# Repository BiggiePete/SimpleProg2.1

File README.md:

# SimpleProg2.1
Simple Prog is a ST-LINK 2.1 esque programmer setup, using a simple PCB board, a 3d printed "clip" design, and a spring, the purpose of this is to intorduce an easier way to program boards, with cheaper footprints

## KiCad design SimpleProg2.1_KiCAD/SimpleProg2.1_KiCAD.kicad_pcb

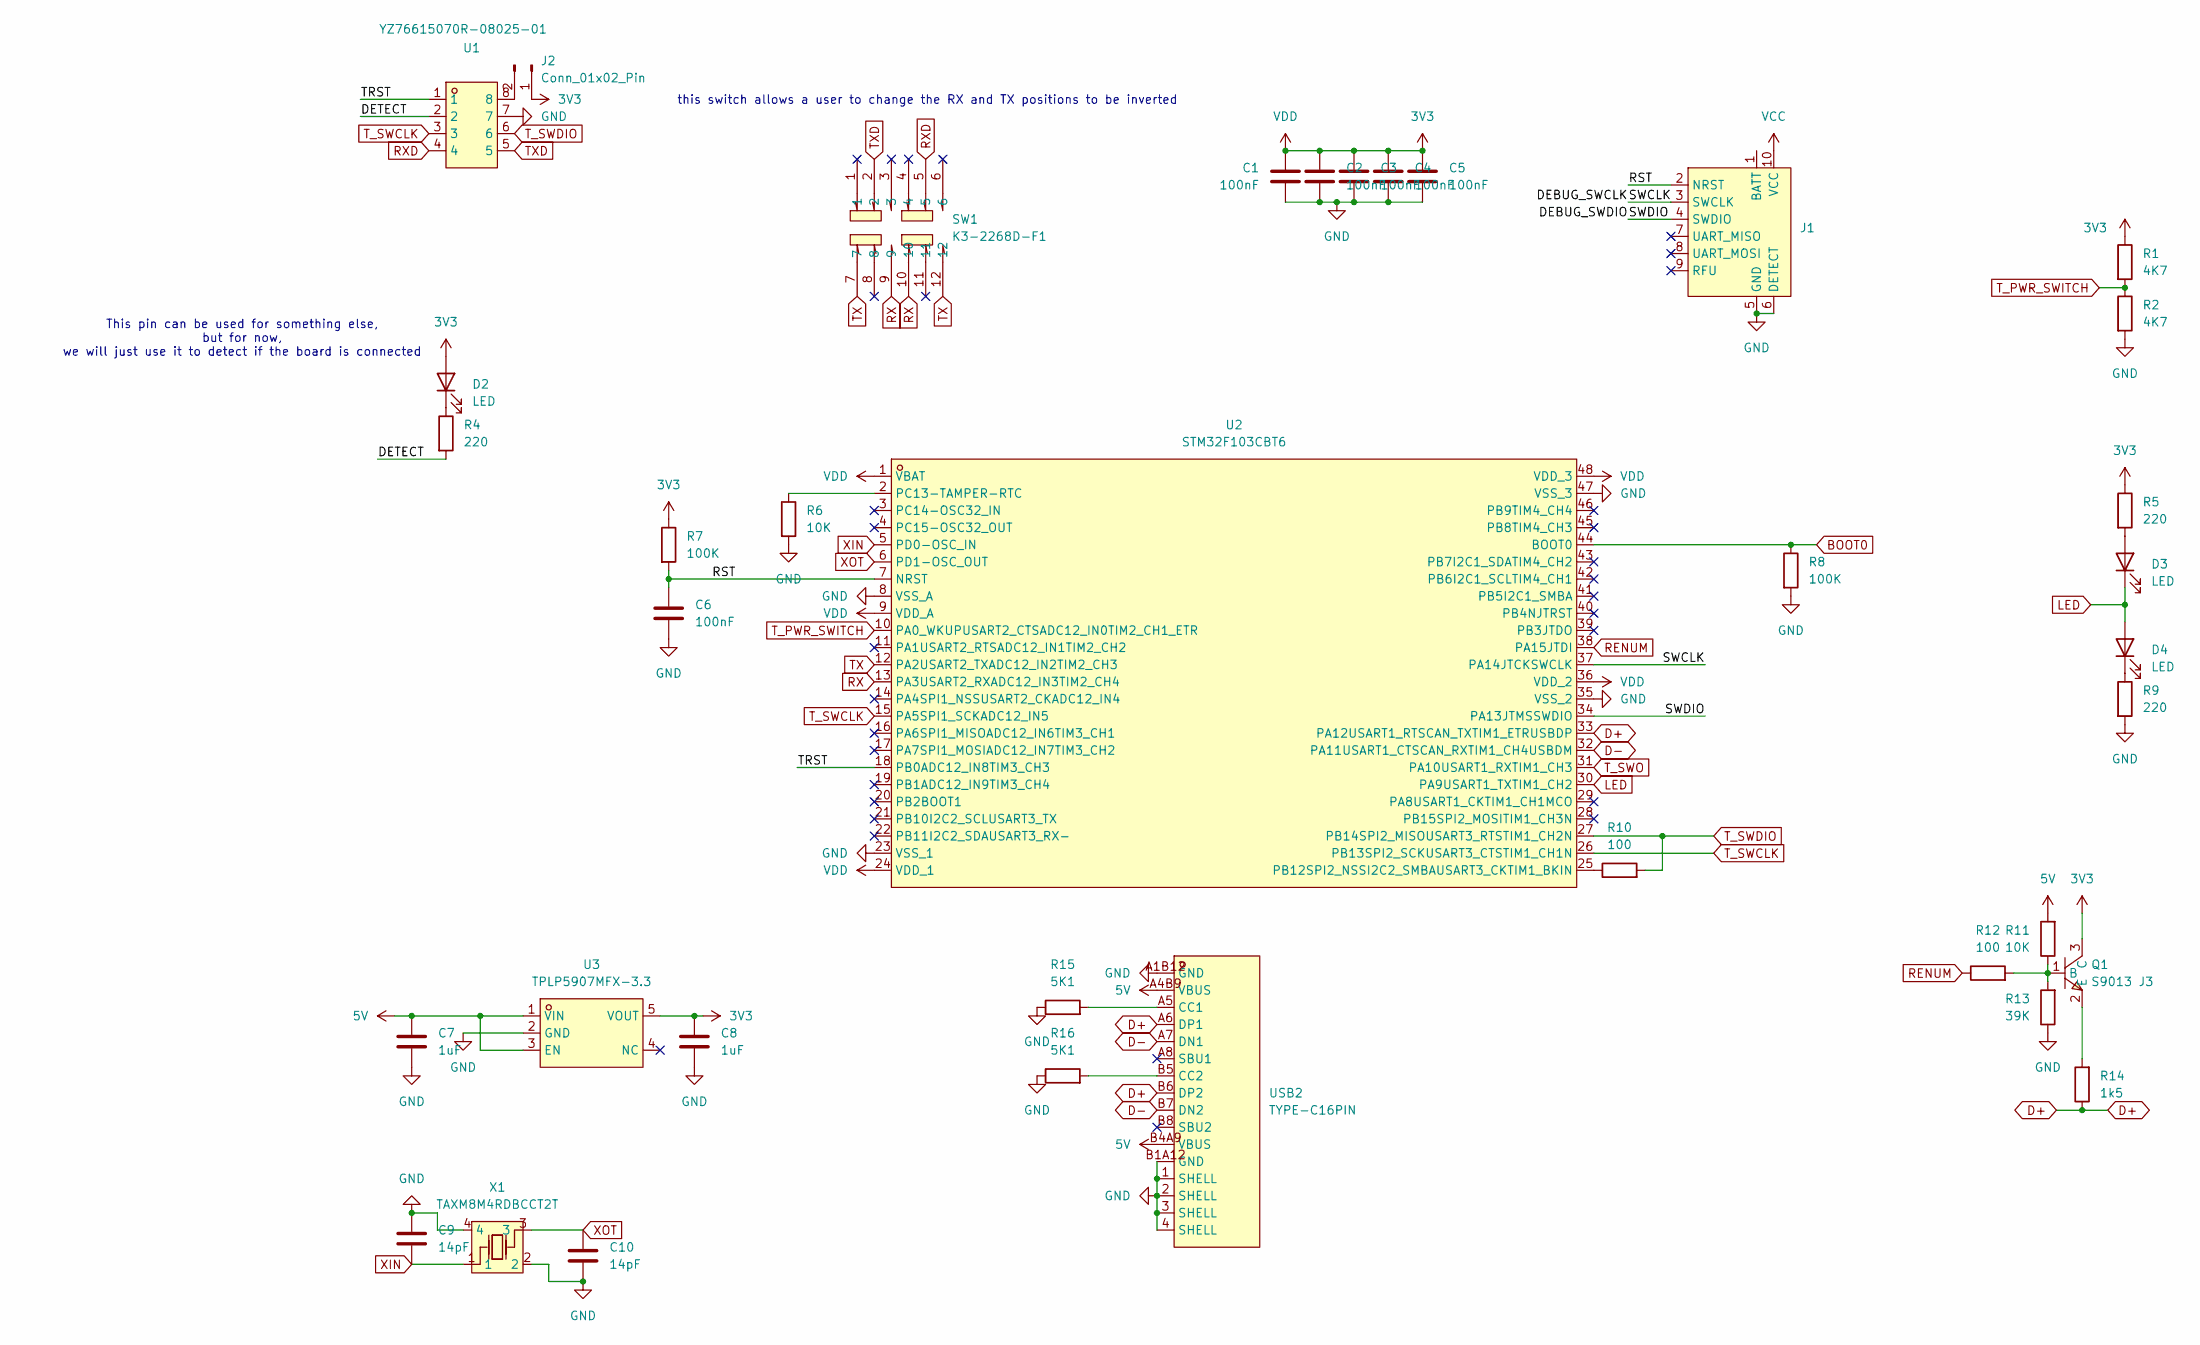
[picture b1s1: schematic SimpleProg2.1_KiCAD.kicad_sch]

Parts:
C1, C2, C3, C4, C5, C6: 100nF; C_0402_1005Metric
C7, C8: 1uF; C_0402_1005Metric
C9, C10: 14pF; C_0402_1005Metric
D2, D3, D4: LED; LED_0805_2012Metric
J1: Tag-Connect_TC2050-IDC-NL_2x05_P1.27mm_Vertical
J2: Conn_01x02_Pin; PinHeader_1x02_P2.54mm_Vertical
Q1: S9013 J3; SOT-23-3_L2.9-W1.3-P1.90-LS2.4-BR; LCSC Part C6749
R1, R2: 4K7; R_0603_1608Metric
R4, R5, R9: 220; R_0603_1608Metric
R6, R11: 10K; R_0603_1608Metric
R7, R8: 100K; R_0603_1608Metric
R10, R12: 100; R_0603_1608Metric
R13: 39K; R_0603_1608Metric
R14: 1k5; R_0603_1608Metric
R15, R16: 5K1; R_0603_1608Metric
SW1: K3-2268D-F1; SW-TH_K3-2268D-F1; LCSC Part C128958
U1: YZ76615070R-08025-01; CONN-SMD_8P-P2.54_YZ76615070R-08025-01; LCSC Part C5280862
U2: STM32F103CBT6; LQFP-48_L7.0-W7.0-P0.50-LS9.0-BL; LCSC Part C8304
U3: TPLP5907MFX-3.3; SOT-23-5_L2.9-W1.6-P0.95-LS2.8-BR; LCSC Part C5370990
USB2: TYPE-C16PIN; USB-C-SMD_TYPE-C16PIN; LCSC Part C393939
X1: TAXM8M4RDBCCT2T; CRYSTAL-SMD_4P-L3.2-W2.5-BL; LCSC Part C400090

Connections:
3V3: C1.1, C2.1, C3.1, C4.1, C5.1, C8.1, D2.2 (A), J2.1, Q1.3 (C), R1.1, R5.1, R7.1, U2.1 (VBAT), U2.9 (VDD_A), U2.24 (VDD_1), U2.36 (VDD_2), U2.48 (VDD_3), U3.5 (VOUT)
5V: C7.1, R11.2, U3.1 (VIN), U3.3 (EN), USB2.A4B9 (VBUS), USB2.B4A9 (VBUS)
/DEBUG_SWCLK: J1.3 (SWCLK), U2.37 (PA14JTCKSWCLK)
/DEBUG_SWDIO: J1.4 (SWDIO), U2.34 (PA13JTMSSWDIO)
/DETECT: R4.2, U1.2
/RST: C6.1, J1.2 (NRST), R7.2, U2.7 (NRST)
/TRST: U1.1, U2.18 (PB0ADC12_IN8TIM3_CH3)
BOOT0: R8.1, U2.44 (BOOT0)
D+: R14.1, U2.33 (PA12USART1_RTSCAN_TXTIM1_ETRUSBDP), USB2.A6 (DP1), USB2.B6 (DP2)
D-: U2.32 (PA11USART1_CTSCAN_RXTIM1_CH4USBDM), USB2.A7 (DN1), USB2.B7 (DN2)
GND: C1.2, C2.2, C3.2, C4.2, C5.2, C6.2, C7.2, C8.2, C9.1, C10.2, J1.5 (GND), J1.6 (DETECT), R2.2, R6.2, R8.2, R9.2, R13.1, R15.1, R16.1, U1.7, U2.8 (VSS_A), U2.23 (VSS_1), U2.35 (VSS_2), U2.47 (VSS_3), U3.2 (GND), USB2.1 (SHELL), USB2.2 (SHELL), USB2.3 (SHELL), USB2.4 (SHELL), USB2.A1B12 (GND), USB2.B1A12 (GND), X1.2, X1.4
LED: D3.1 (K), D4.2 (A), U2.30 (PA9USART1_TXTIM1_CH2)
unnamed: D2.1 (K), R4.1
unnamed: D3.2 (A), R5.2
unnamed: D4.1 (K), R9.1
unnamed: J2.2, U1.8
unnamed: Q1.1 (B), R11.1, R12.2, R13.2
unnamed: Q1.2 (E), R14.2
unnamed: R10.1, U2.25 (PB12SPI2_NSSI2C2_SMBAUSART3_CKTIM1_BKIN)
unnamed: R6.1, U2.2 (PC13-TAMPER-RTC)
unnamed: R15.2, USB2.A5 (CC1)
unnamed: R16.2, USB2.B5 (CC2)
RENUM: R12.1, U2.38 (PA15JTDI)
RX: SW1.9, SW1.10, U2.13 (PA3USART2_RXADC12_IN3TIM2_CH4)
RXD: SW1.5, U1.4
TX: SW1.7, SW1.12, U2.12 (PA2USART2_TXADC12_IN2TIM2_CH3)
TXD: SW1.2, U1.5
T_PWR_SWITCH: R1.2, R2.1, U2.10 (PA0_WKUPUSART2_CTSADC12_IN0TIM2_CH1_ETR)
T_SWCLK: U1.3, U2.15 (PA5SPI1_SCKADC12_IN5), U2.26 (PB13SPI2_SCKUSART3_CTSTIM1_CH1N)
T_SWDIO: R10.2, U1.6, U2.27 (PB14SPI2_MISOUSART3_RTSTIM1_CH2N)
T_SWO: U2.31 (PA10USART1_RXTIM1_CH3)
XIN: C9.2, U2.5 (PD0-OSC_IN), X1.1
XOT: C10.1, U2.6 (PD1-OSC_OUT), X1.3

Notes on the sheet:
this switch allows a user to change the RX and TX positions to be inverted
This pin can be used for something else, but for now, we will just use it to detect if the board is connected

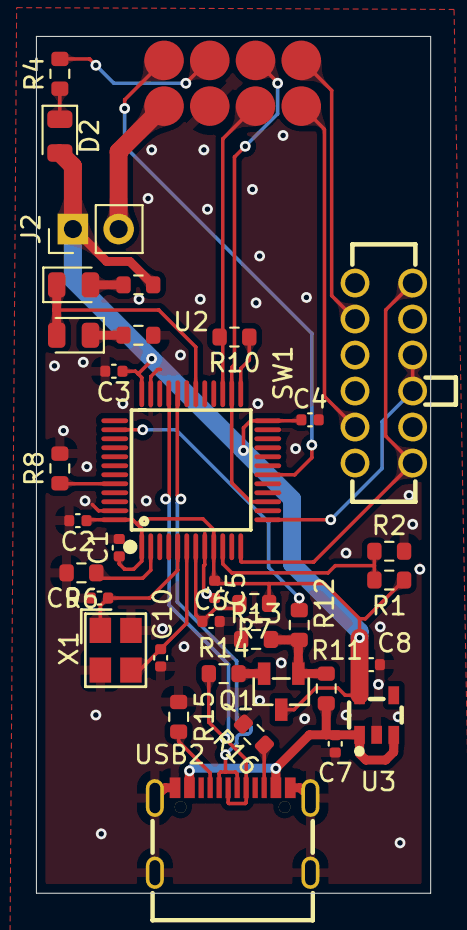
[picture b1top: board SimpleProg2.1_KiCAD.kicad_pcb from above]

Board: 2 copper layers, 21.9 x 47.6 mm, 36 parts (0 on the bottom side), 30 nets.

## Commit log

2025-08-14 prospectus board based on existing design
